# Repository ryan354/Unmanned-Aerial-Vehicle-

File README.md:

# Unmanned-Aerial-Vehicle-

Singapore Amazing Flying Machine Competition (SAFMC) is a Quadcopter or drone competition organized by DSO National Laboratories, Science Center Singapore and supported by the Ministry of Defense Singapore (MINDEF). In development of quadcopter many problems are found, such as collisions or crashes against obstacles and other quadcopter on the fly. This project discusses a PID control method for manipulating pitch and roll based on the proximity sensor as collision avoidance. The information obtained is then processed by PID control before entering the quadcopter flight controller. every quadcopter movement will be observed and evaluated to obtain stable movement. Use of wireless communication and telemetry data to facilitate the control of quadcopter with ground stations

okay let's dive into the project!!!!

1. UAV Design

2. PCB (Printed Circuit Boards) Deisgn 

3. System Flowchart

Trial Video.

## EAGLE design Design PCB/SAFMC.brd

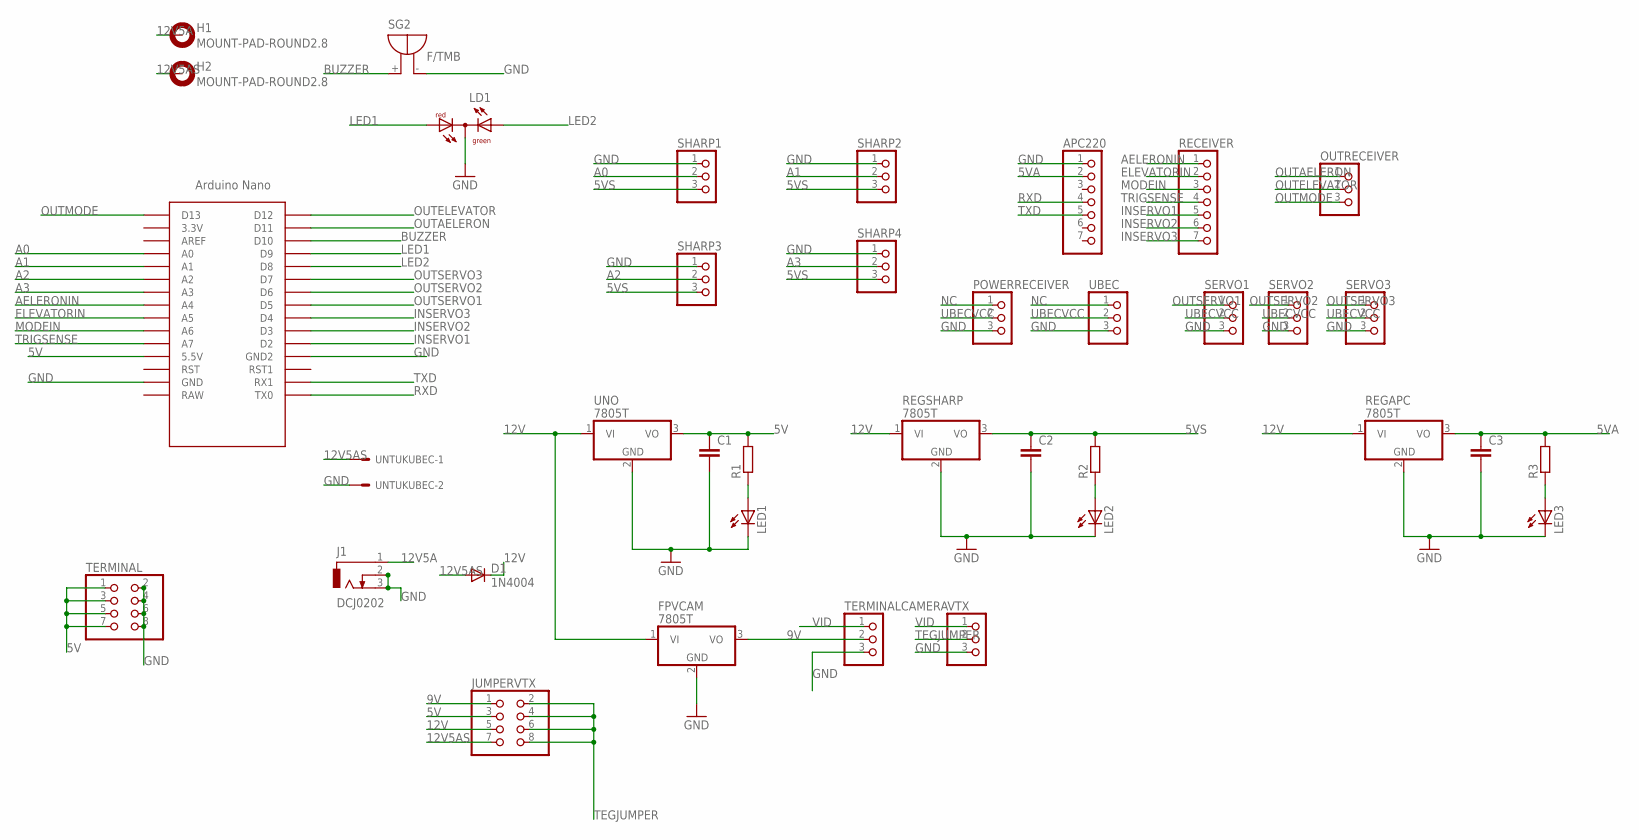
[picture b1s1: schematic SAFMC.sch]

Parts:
APC220: PINHD-1X7; 1X07
C1, C2, C3: C5/2.5; C5B2.5
D1: 1N4004; DO41-10
FPVCAM: 7805T; TO220H
H1, H2: MOUNT-PAD-ROUND2.8; 2,8-PAD
J1: DCJ0202
JUMPERVTX: PINHD-2X4; 2X04
LD1: DUOLED-RG-C; DUOLED-C-5MM
LED1, LED2, LED3: LED5MM
OUTRECEIVER: PINHD-1X3; 1X03
POWERRECEIVER: PINHD-1X3; 1X03
R1, R2, R3: R0204/7; 0204/7
RECEIVER: PINHD-1X7; 1X07
REGAPC: 7805T; TO220H
REGSHARP: 7805T; TO220H
SERVO1, SERVO2, SERVO3: PINHD-1X3; 1X03
SG2: F/TMB
SHARP1, SHARP2, SHARP3, SHARP4: PINHD-1X3; 1X03
TERMINAL: PINHD-2X4; 2X04
TERMINALCAMERA: PINHD-1X3; 1X03
U$2: NANO
UBEC: PINHD-1X3; 1X03
UNO: 7805T; TO220H
UNTUKUBEC: KK-156-2
VTX: PINHD-1X3; 1X03

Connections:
5V: C1.1, JUMPERVTX.3, R1.2, TERMINAL.1, TERMINAL.3, TERMINAL.5, TERMINAL.7, U$2.5V (5.5V), UNO.3 (VO)
5VA: APC220.2, C3.1, R3.2, REGAPC.3 (VO)
5VS: C2.1, R2.2, REGSHARP.3 (VO), SHARP1.3, SHARP2.3, SHARP3.3, SHARP4.3
9V: FPVCAM.3 (VO), JUMPERVTX.1, TERMINALCAMERA.2
12V: D1.C, FPVCAM.1 (VI), JUMPERVTX.5, REGAPC.1 (VI), REGSHARP.1 (VI), UNO.1 (VI)
12V5A: H1.B2,8, J1.1
12V5AS: D1.A, H2.B2,8, JUMPERVTX.7, UNTUKUBEC.1
A0: SHARP1.2, U$2.A0
A1: SHARP2.2, U$2.A1
A2: SHARP3.2, U$2.A2
A3: SHARP4.2, U$2.A3
AELERONIN: RECEIVER.1, U$2.A4
BUZZER: SG2.+, U$2.D10
ELEVATORIN: RECEIVER.2, U$2.A5
GND: APC220.1, C1.2, C2.2, C3.2, FPVCAM.2 (GND), J1.2, J1.3, LD1.C, LED1.K (C), LED2.K (C), LED3.K (C), POWERRECEIVER.3, REGAPC.2 (GND), REGSHARP.2 (GND), SERVO1.3, SERVO2.3, SERVO3.3, SG2.-, SHARP1.1, SHARP2.1, SHARP3.1, SHARP4.1, TERMINAL.2, TERMINAL.4, TERMINAL.6, TERMINAL.8, TERMINALCAMERA.3, U$2.GND, U$2.GND1 (GND2), UBEC.3, UNO.2 (GND), UNTUKUBEC.2, VTX.3
INSERVO1: RECEIVER.5, U$2.D2
INSERVO2: RECEIVER.6, U$2.D3
INSERVO3: RECEIVER.7, U$2.D4
LED1: LD1.AR, U$2.D9
LED2: LD1.AX (AG), U$2.D8
MODEIN: RECEIVER.3, U$2.A6
unnamed: LED3.A, R3.1
unnamed: LED1.A, R1.1
unnamed: LED2.A, R2.1
NC: POWERRECEIVER.1, UBEC.1
OUTAELERON: OUTRECEIVER.1, U$2.D11
OUTELEVATOR: OUTRECEIVER.2, U$2.D12
OUTMODE: OUTRECEIVER.3, U$2.D13
OUTSERVO1: SERVO1.1, U$2.D5
OUTSERVO2: SERVO2.1, U$2.D6
OUTSERVO3: SERVO3.1, U$2.D7
RXD: APC220.4, U$2.TX0
TEGJUMPER: JUMPERVTX.2, JUMPERVTX.4, JUMPERVTX.6, JUMPERVTX.8, VTX.2
TRIGSENSE: RECEIVER.4, U$2.A7
TXD: APC220.5, U$2.RX1
UBECVCC: POWERRECEIVER.2, SERVO1.2, SERVO2.2, SERVO3.2, UBEC.2
VID: TERMINALCAMERA.1, VTX.1

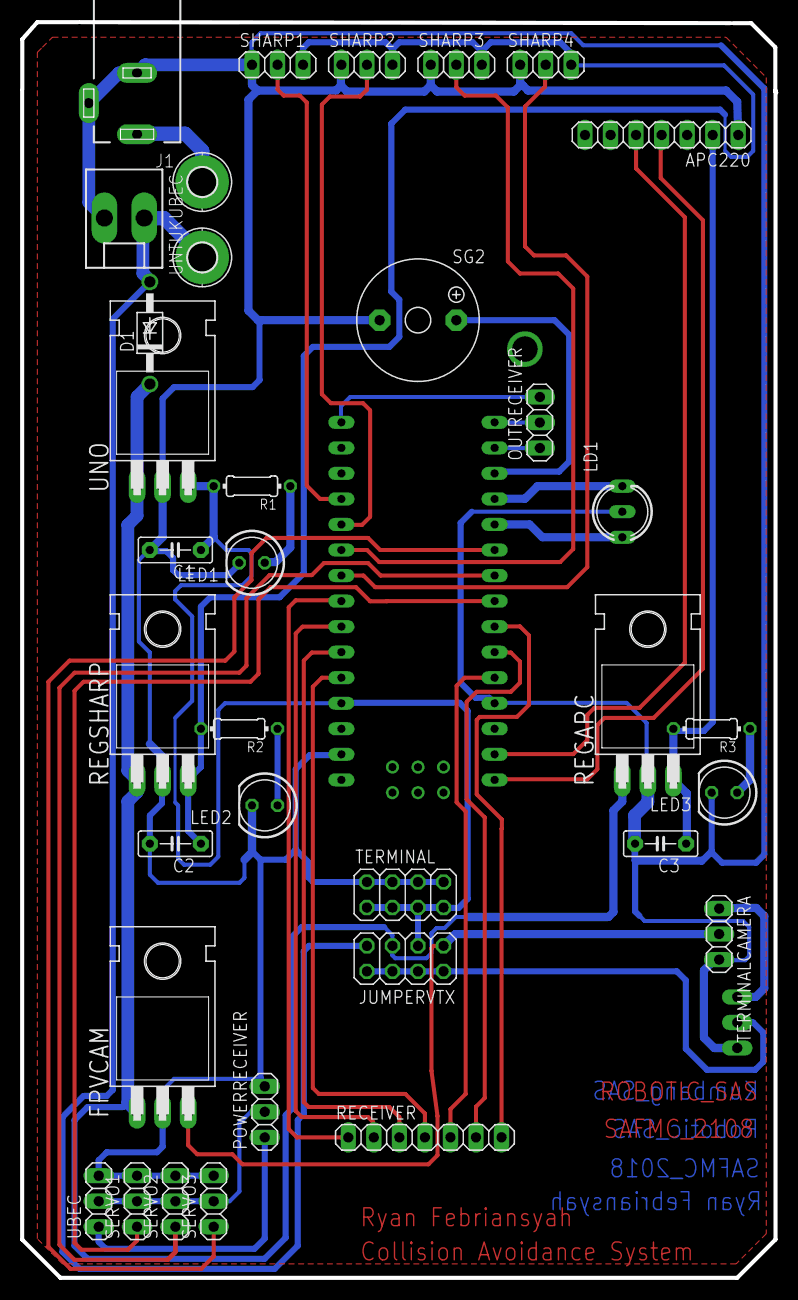
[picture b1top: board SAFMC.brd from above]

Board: 2 copper layers, 75.0 x 124.9 mm, 37 parts (1 on the bottom side), 37 nets.

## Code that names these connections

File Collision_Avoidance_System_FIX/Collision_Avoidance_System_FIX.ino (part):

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//INPUT sensor sharp
int ir[4] = {A0, A1, A2, A3};
//INPUT Receiver
#define aeleronIN  A4
#define elevatorIN  A5
#define modeIN  2
#define triggerIN  3
#define inmode  9
//OUTPUT Receiver
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#define outservofree 7
//optional tambahan
#define lampu1 8
#define buzzer 10


int left, front, right, back;//nilai sensor
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    pinMode(ir[i], INPUT);
  }
  //receiver pin function declare
  pinMode(aeleronIN, INPUT);
  pinMode(elevatorIN, INPUT);
  pinMode(modeIN, INPUT);
  pinMode(triggerIN, INPUT);
  pinMode(inmode, INPUT);

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  pinMode(outservofree, OUTPUT);

  //optional pin function declare
  pinMode(buzzer, OUTPUT);
  pinMode(lampu1, OUTPUT);
  digitalWrite(buzzer, LOW);
  digitalWrite(lampu1, LOW);
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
